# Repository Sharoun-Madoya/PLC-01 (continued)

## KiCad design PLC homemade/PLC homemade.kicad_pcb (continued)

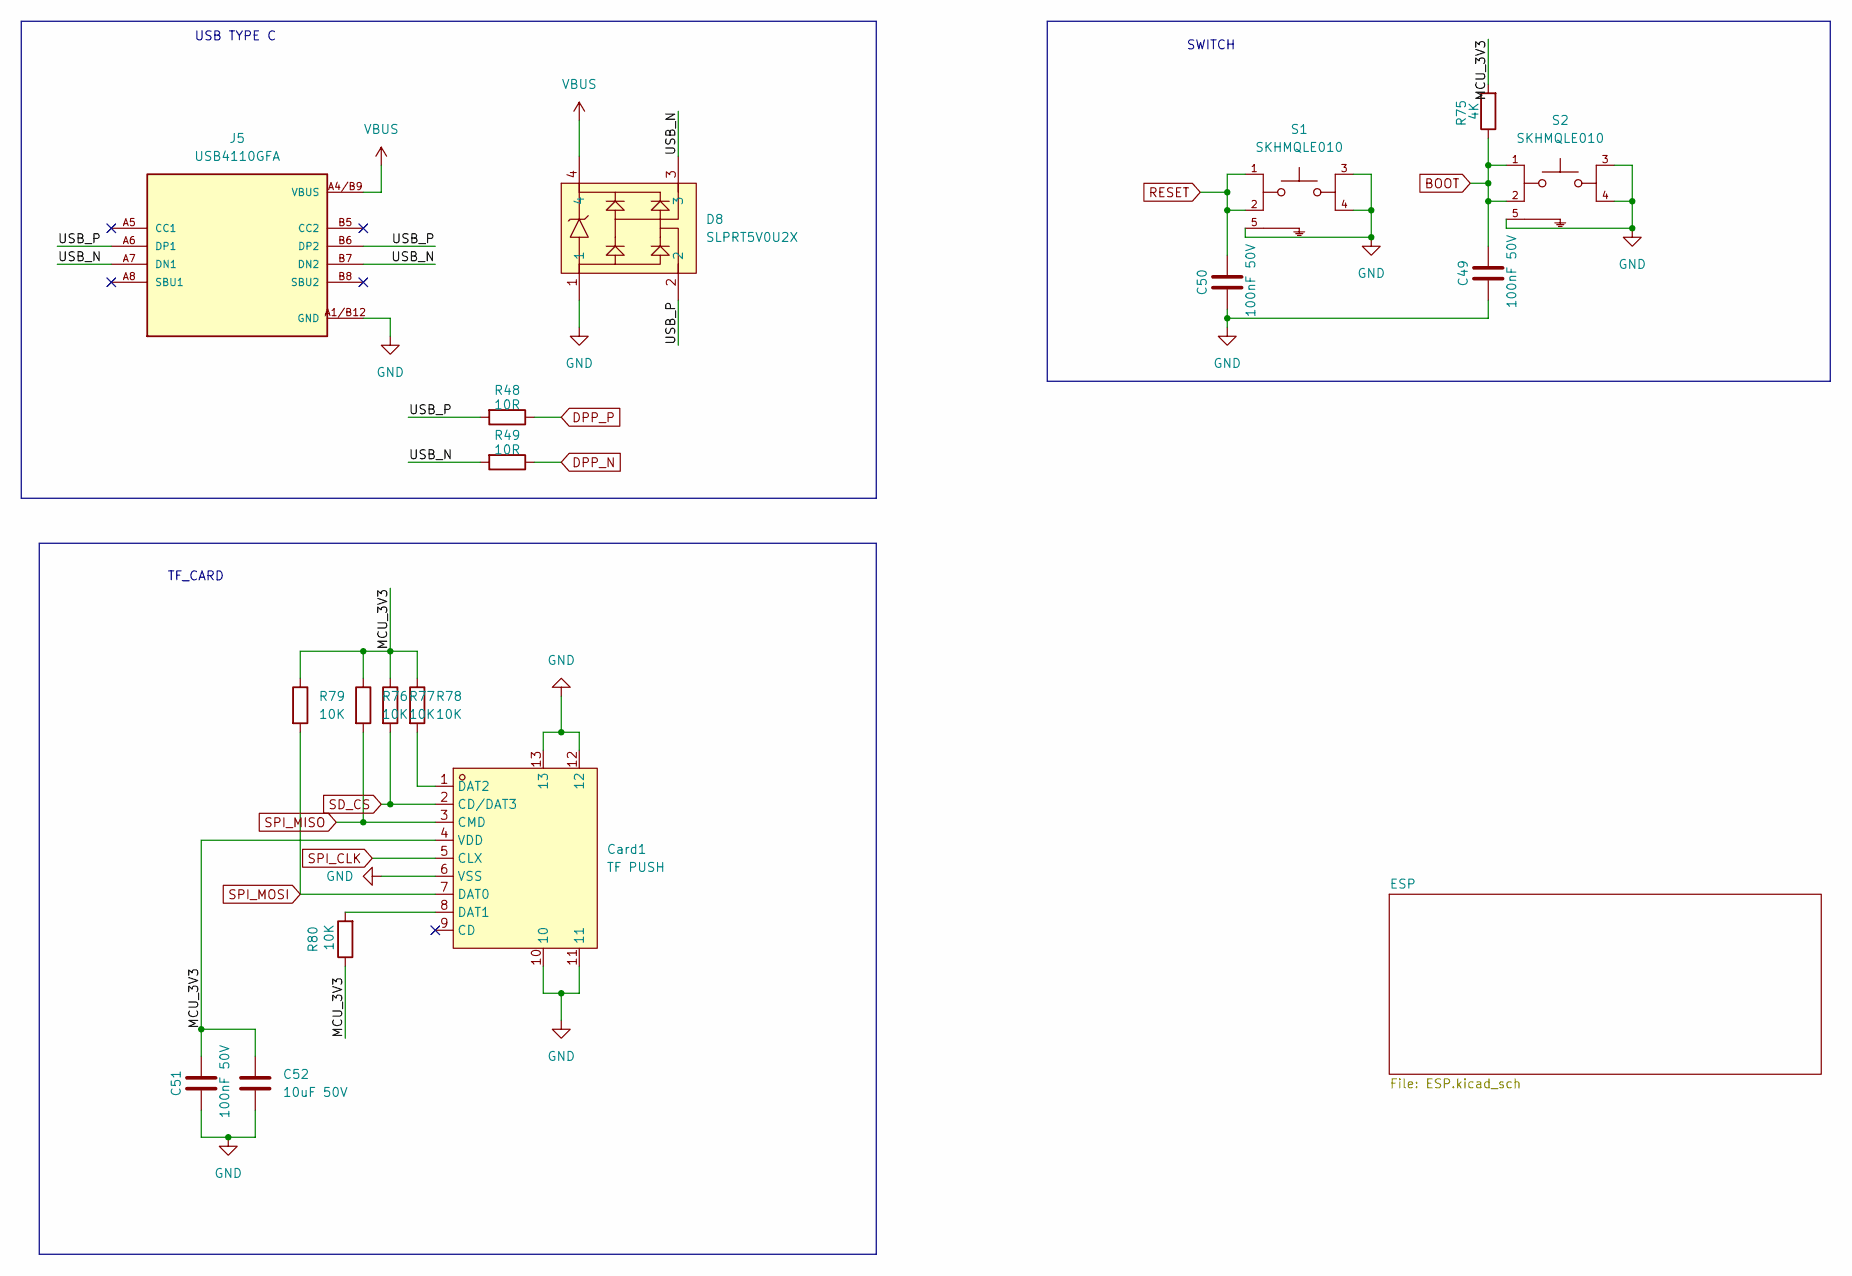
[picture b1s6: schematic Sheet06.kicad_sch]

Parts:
C49, C50, C51: 100nF 50V; C_01005_0402Metric
C52: 10uF 50V; C_0201_0603Metric
Card1: TF PUSH; TF-SMD_TF-PUSH; LCSC Part C393941
D8: SLPRT5V0U2X; SOT-143-4_L2.9-W1.3-P1.90-LS2.4-BL; LCSC Part C2918937
J5: USB4110GFA; GCT_USB4110GFA
R48, R49: 10R; R_01005_0402Metric
R75: 4K; R_01005_0402Metric
R76, R77, R78, R79, R80: 10K; R_01005_0402Metric
S1, S2: SKHMQLE010; SW_SKHMQLE010

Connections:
/ETHERNET/Sheet03/Sheet04/OUTPUT/Sheet06/MCU_3V3: C51.2, C52.1, Card1.4 (VDD), R75.2, R76.1, R77.1, R78.1, R79.1, R80.1
/ETHERNET/Sheet03/Sheet04/OUTPUT/Sheet06/USB_N: D8.3, J5.A7 (DN1), J5.B7 (DN2), R49.2
/ETHERNET/Sheet03/Sheet04/OUTPUT/Sheet06/USB_P: D8.2, J5.A6 (DP1), J5.B6 (DP2), R48.2
AGND: C49.1, C50.1, C51.1, C52.2, Card1.6 (VSS), Card1.10, Card1.11, Card1.12, Card1.13, D8.1, J5.A1/B12 (GND), J5.B1/A12 (GND), J5.S1 (GND), J5.S2 (GND), J5.S3 (GND), J5.S4 (GND), S1.3, S1.4, S1.5, S2.3, S2.4, S2.5; also elsewhere on the board
BOOT: C49.2, R75.1, S2.1, S2.2; also elsewhere on the board
DPP_N: R49.1; also elsewhere on the board
DPP_P: R48.1; also elsewhere on the board
unnamed: Card1.8 (DAT1), R80.2
unnamed: Card1.1 (DAT2), R78.2
RESET: C50.2, S1.1, S1.2; also elsewhere on the board
SD_CS: Card1.2 (CD/DAT3), R77.2
SPI_CLK: Card1.5 (CLX); also elsewhere on the board
SPI_MISO: Card1.3 (CMD), R76.2; also elsewhere on the board
SPI_MOSI: Card1.7 (DAT0), R79.2; also elsewhere on the board
VBUS: D8.4, J5.A4/B9 (VBUS), J5.B4/A9 (VBUS)

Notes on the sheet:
SWITCH
TF_CARD
USB TYPE C

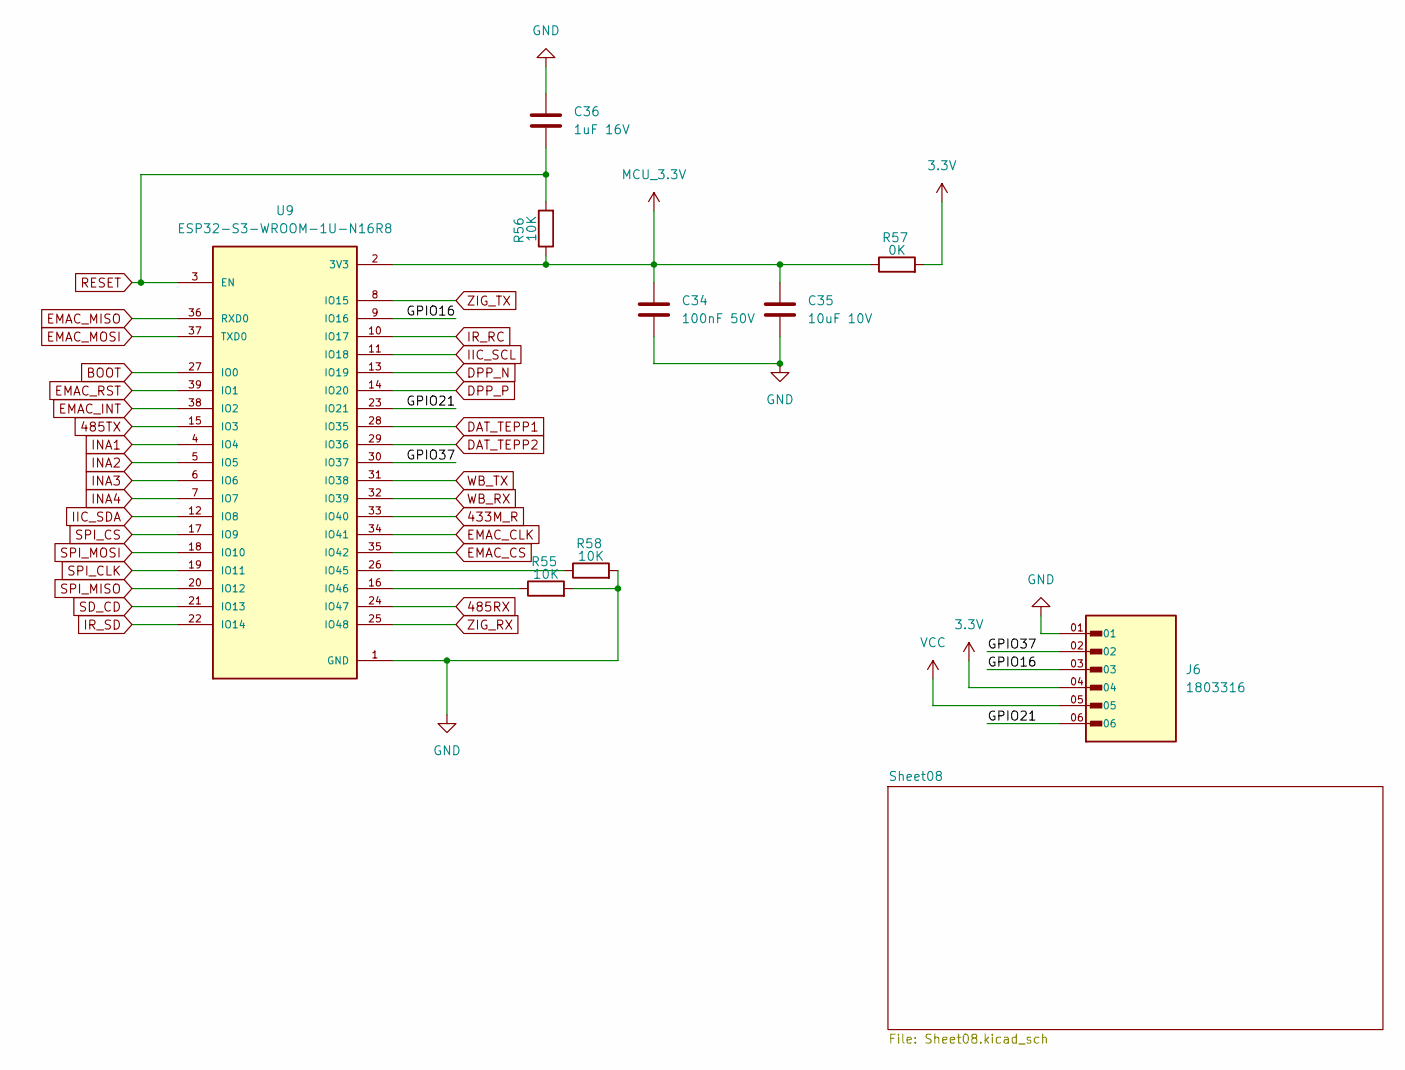
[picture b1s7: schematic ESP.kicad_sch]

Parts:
C34: 100nF 50V; C_01005_0402Metric
C35: 10uF 10V; C_0201_0603Metric
C36: 1uF 16V; C_0201_0603Metric
J6: 1803316; PHOENIX_1803316; PARTREV 08.06.2015
R55, R56, R58: 10K; R_01005_0402Metric
R57: 0K; R_0402_1005Metric
U9: ESP32-S3-WROOM-1U-N16R8; XCVR_ESP32-S3-WROOM-1U-N16R8; PARTREV v1.1

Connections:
3.3V: J6.04, R57.2; also elsewhere on the board
433M_R: U9.33 (IO40)
485RX: U9.24 (IO47); also elsewhere on the board
485TX: U9.15 (IO3); also elsewhere on the board
/ETHERNET/Sheet03/Sheet04/OUTPUT/Sheet06/ESP/GPIO16: J6.03, U9.9 (IO16)
/ETHERNET/Sheet03/Sheet04/OUTPUT/Sheet06/ESP/GPIO21: J6.06, U9.23 (IO21)
/ETHERNET/Sheet03/Sheet04/OUTPUT/Sheet06/ESP/GPIO37: J6.02, U9.30 (IO37)
AGND: C34.2, C35.2, C36.1, J6.01, R55.2, R58.2, U9.1 (GND), U9.40 (GND), U9.41_1 (GND), U9.41_2 (GND), U9.41_3 (GND), U9.41_4 (GND), U9.41_5 (GND), U9.41_6 (GND), U9.41_7 (GND), U9.41_8 (GND), U9.41_9 (GND); also elsewhere on the board
BOOT: U9.27 (IO0); also elsewhere on the board
DAT_TEPP1: U9.28 (IO35); also elsewhere on the board
DAT_TEPP2: U9.29 (IO36); also elsewhere on the board
DPP_N: U9.13 (IO19); also elsewhere on the board
DPP_P: U9.14 (IO20); also elsewhere on the board
EMAC_CLK: U9.34 (IO41); also elsewhere on the board
EMAC_CS: U9.35 (IO42); also elsewhere on the board
EMAC_INT: U9.38 (IO2); also elsewhere on the board
EMAC_MISO: U9.36 (RXD0); also elsewhere on the board
EMAC_MOSI: U9.37 (TXD0); also elsewhere on the board
EMAC_RST: U9.39 (IO1); also elsewhere on the board
IIC_SCL: U9.11 (IO18); also elsewhere on the board
IIC_SDA: U9.12 (IO8); also elsewhere on the board
INA1: U9.4 (IO4); also elsewhere on the board
INA2: U9.5 (IO5); also elsewhere on the board
INA3: U9.6 (IO6); also elsewhere on the board
INA4: U9.7 (IO7); also elsewhere on the board
IR_RC: U9.10 (IO17)
IR_SD: U9.22 (IO14)
MCU_3.3V: C34.1, C35.1, R56.1, R57.1, U9.2 (3V3)
unnamed: R58.1, U9.26 (IO45)
unnamed: R55.1, U9.16 (IO46)
RESET: C36.2, R56.2, U9.3 (EN); also elsewhere on the board
SD_CD: U9.21 (IO13)
SPI_CLK: U9.19 (IO11); also elsewhere on the board
SPI_CS: U9.17 (IO9)
SPI_MISO: U9.20 (IO12); also elsewhere on the board
SPI_MOSI: U9.18 (IO10); also elsewhere on the board
VCC: J6.05; also elsewhere on the board
WB_RX: U9.32 (IO39)
WB_TX: U9.31 (IO38)
ZIG_RX: U9.25 (IO48)
ZIG_TX: U9.8 (IO15)

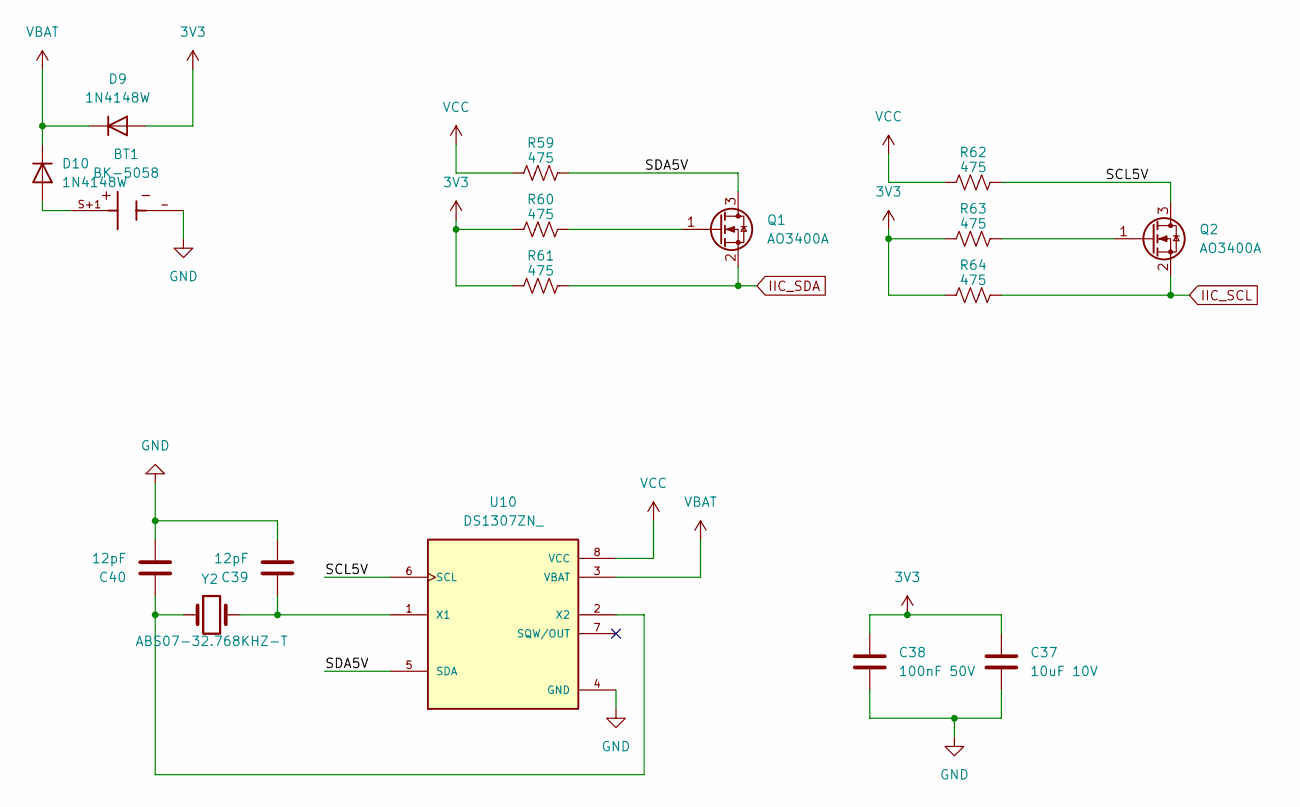
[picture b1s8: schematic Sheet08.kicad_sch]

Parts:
BT1: BK-5058; BatteryHolder_Seiko_MS621F; PARTREV M
C37: 10uF 10V; C_0201_0603Metric
C38: 100nF 50V; C_0201_0603Metric
C39, C40: 12pF; C_01005_0402Metric
D9, D10: 1N4148W; D_SOD-123
Q1, Q2: AO3400A; SOT-23
R59, R60, R61, R62, R63, R64: 475; R_01005_0402Metric
U10: DS1307ZN_; SOIC127P600X175-8N
Y2: ABS07-32.768KHZ-T; Crystal_SMD_5032-2Pin_5.0x3.2mm

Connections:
3V3: C37.1, C38.1, D9.2 (A), R60.1, R61.1, R63.1, R64.1
/ETHERNET/Sheet03/Sheet04/OUTPUT/Sheet06/ESP/Sheet08/SCL5V: Q2.3 (D), R62.2, U10.6 (SCL)
/ETHERNET/Sheet03/Sheet04/OUTPUT/Sheet06/ESP/Sheet08/SDA5V: Q1.3 (D), R59.2, U10.5 (SDA)
AGND: BT1.-, C37.2, C38.2, C39.2, C40.2, U10.4 (GND); also elsewhere on the board
IIC_SCL: Q2.2 (S), R64.2; also elsewhere on the board
IIC_SDA: Q1.2 (S), R61.2; also elsewhere on the board
unnamed: BT1.S+1, BT1.S+2, D10.2 (A)
unnamed: Q1.1 (G), R60.2
unnamed: Q2.1 (G), R63.2
unnamed: C39.1, U10.1 (X1), Y2.2
unnamed: C40.1, U10.2 (X2), Y2.1
VBAT: D9.1 (K), D10.1 (K), U10.3 (VBAT)
VCC: R59.1, R62.1, U10.8 (VCC); also elsewhere on the board

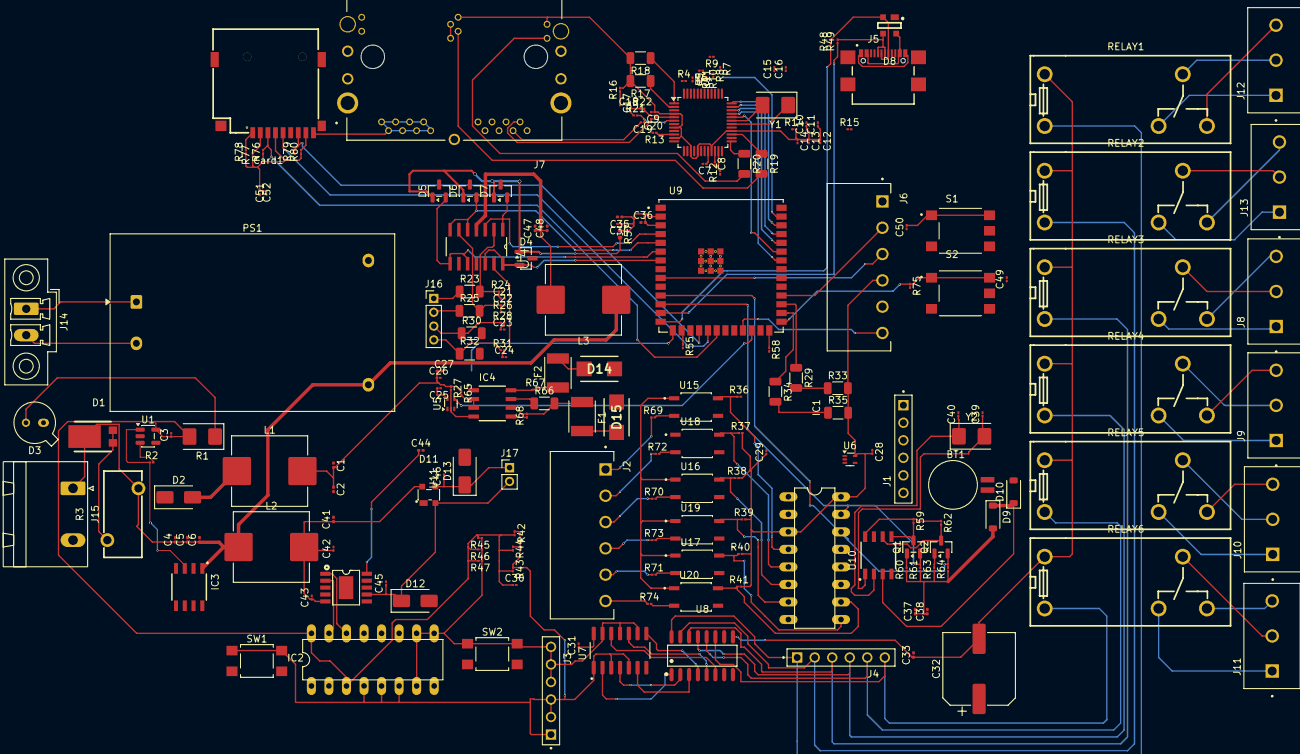
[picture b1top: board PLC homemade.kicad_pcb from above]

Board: 2 copper layers, 201 parts (0 on the bottom side), 156 nets.

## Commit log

2026-01-13 initial schematic
2026-01-16 :tada: completed power side of the schematic
2026-01-16 :hammer: added ethernet page of the herachial sheet
2026-01-16 :chart_with_upwards_trend:COMPLETED EHERNET, left 1 component out
2026-01-16 :spanner:atarted on rs485 interface and ADC
2026-01-17 :zap: completing basics of rs485
2026-01-18 :spanner:At interfaces
2026-01-18 :rocket: started on OUTPUT
2026-01-18 :rocket: completed BC847BDW1T1G
2026-01-18 ::construction_worker:: Started on esp
2026-01-18 ::construction_worker:: Completed esp
2026-01-18 :green_heart: CoRRECTED pOWER eRRORS
2026-01-19 :see_no_evil: created last page details
2026-01-20 :art: grouped Power section
2026-01-20 :art: COMPLETED SHEET3
2026-01-20 :art: COMPLETED SHEET4
2026-01-20 :tada: COMPLETED SHEET5
2026-01-20 :clown_face:Completed schematic
2026-01-22 :clown_face: changed HEIRACHIAL to global
2026-01-22 :memo: Added Read me info
2026-01-22 :tada: Added small changes
2026-01-23 :tada: Run Electrical rule checker All errors corrected
2026-02-11 :memo: Started On editor , Ethernet and Power Sector
2026-02-11 :ambulance:2CH AND ADC
2026-02-12 :ambulance:2output and usbc
2026-02-15 :tada:Completed most placements in groups
2026-02-15 :tada: Arranged the editing
2026-02-16 :ambulance: Changed the 5 footprint error
2026-02-17 :art: wiring componets done
